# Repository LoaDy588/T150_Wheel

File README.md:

# T150 Wheel adapter board

This board connects to the Thrustmaster T150 wheel base and interfaces up to 15 buttons, in the same way as the original wheel.

You can connect any switch or button to this, but it doesn't support potentiometers. Each connection is labeled by the original button name on bottom of the board.

The base connects via 6 pins - the bottom of the board has the proper way to connect the original cable by color of the conductor(I don't know if all T150 bases use the same color scheme though, so this might not be true).

Removing the original wheel from the base is easy - there are two big screws on the shaft, unscrew those and slide the wheel off. If you want to make quickchange wheels, I suggest cutting the cable in half and adding some 6pin connectors to it, so that you don't have to disassemble the rest of the wheel to disconnect the cable.

## BOM
 * 3x NXP HEF4021BT - shift registers, SOP-16 package
 * 22x 100k 0805 SMD resistor
 * (Optional) 0.1" headers for connecting - you can also solder to the pads directly

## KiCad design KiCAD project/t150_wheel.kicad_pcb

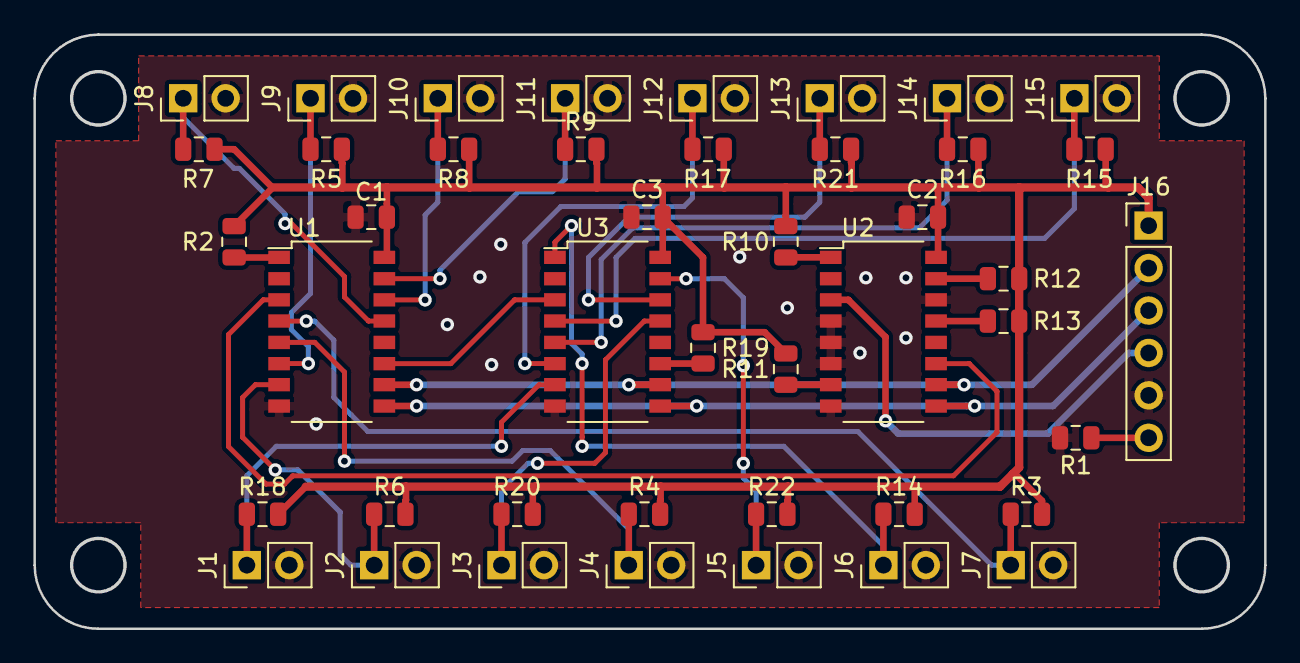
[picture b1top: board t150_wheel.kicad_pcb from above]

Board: 2 copper layers, 73.6 x 35.5 mm, 44 parts (0 on the bottom side), 29 nets.

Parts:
C1, C2, C3: 100nF; C_0805_2012Metric
J1, J2, J3, J4, J5, J6, J7, J8, J9, J10, J11, J12, J13, J14, J15: Conn_01x02; PinHeader_1x02_P2.54mm_Vertical
J16: BASE_CON; PinHeader_1x06_P2.54mm_Vertical
R1, R2, R3, R4, R5, R6, R7, R8, R9, R10, R11, R12, R13, R14, R15, R16, R17, R18, R19, R20, R21, R22: 100K; R_0805_2012Metric
U1, U2, U3: HEF4021B; SOP-16_4.4x10.4mm_P1.27mm

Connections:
CIRCLE: J10.1, R8.1, U1.14
CROSS: J11.1, R9.1, U1.15
D1_LINE: J16.2, U1.10, U2.10, U3.10
D2_LINE: J16.3, U1.9, U2.9, U3.9
D3_LINE: J16.4, U2.3
DPAD_DOWN: J13.1, R21.1, U3.14
DPAD_LEFT: J14.1, R16.1, U3.5
DPAD_RIGHT: J15.1, R15.1, U3.4
DPAD_UP: J12.1, R17.1, U3.6
GND: C1.2, C2.2, C3.2, J1.2, J2.2, J3.2, J4.2, J5.2, J6.2, J7.2, J8.2, J9.2, J10.2, J11.2, J12.2, J13.2, J14.2, J15.2, J16.5, R1.2, U1.8, U2.4, U2.5, U2.6, U2.8, U2.14, U3.8
L2: J1.1, R18.1, U3.7
LEFT_PADDLE: J3.1, R20.1, U3.13
unnamed: J16.6, R1.1
unnamed: R2.1, U1.1
unnamed: R10.1, U2.1
unnamed: R11.1, U2.7
unnamed: R12.1, U2.15
unnamed: R13.1, U2.13
unnamed: R19.1, U3.11
unnamed: U1.3, U2.11
unnamed: U1.11, U3.3
PS_BUTTON: J5.1, R22.1, U3.15
R2: J2.1, R6.1, U1.7
RIGHT_PADDLE: J4.1, R4.1, U1.5
SELECT: J6.1, R14.1, U3.1
SQUARE: J8.1, R7.1, U1.13
START: J7.1, R3.1, U1.4
TRIANGLE: J9.1, R5.1, U1.6
VDD: C1.1, C2.1, C3.1, J16.1, R2.2, R3.2, R4.2, R5.2, R6.2, R7.2, R8.2, R9.2, R10.2, R11.2, R12.2, R13.2, R14.2, R15.2, R16.2, R17.2, R18.2, R19.2, R20.2, R21.2, R22.2, U1.16, U2.16, U3.16

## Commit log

2018-08-24 KiCAD files
2018-08-24 rename
